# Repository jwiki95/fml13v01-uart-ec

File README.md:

## Expansion Card for UART Channel on DC RISC-V Mainboard

This is a KiCad Project with a basic schematic and board layout for connecting to the UART channel 
on the FML13V01 RISC-V Mainboard. This layout is intended to be used with any USB-UART controller
using 0.1 inch pin headers or the Raspberry Pi Debug Probe UART channel using the included JST
cable. This project started with the 
[Expansion Card template](https://github.com/FrameworkComputer/ExpansionCards/tree/main/Electrical) 
provided by Framework and the 
[documented pinout](https://github.com/DC-DeepComputing/Framework/blob/main/FML13V01/Framework%20Serial%20Port%20Connection%20Guide.pdf)
from Deep Computing. This design is a work-in-progress as I have not had samples manufactured at this time.

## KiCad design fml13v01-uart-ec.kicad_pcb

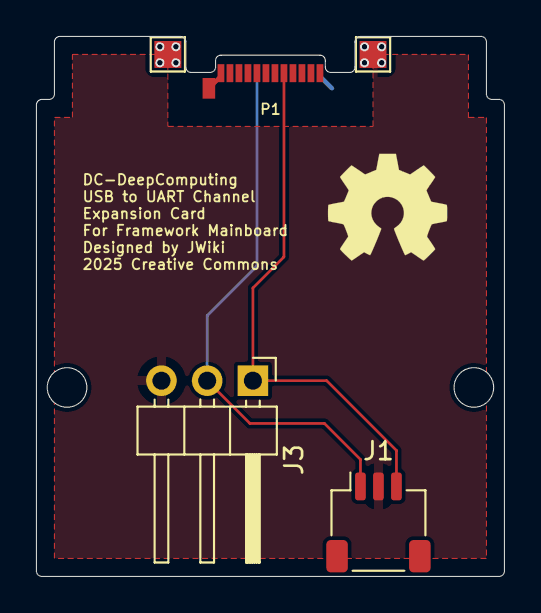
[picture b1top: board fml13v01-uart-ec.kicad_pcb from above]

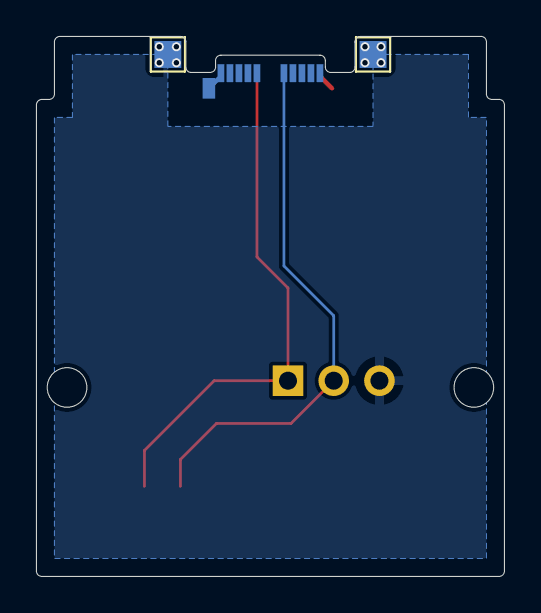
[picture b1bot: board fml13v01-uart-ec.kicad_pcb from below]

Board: 2 copper layers, 26.0 x 30.0 mm, 9 parts (2 on the bottom side), 4 nets.

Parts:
H1, H2: MountingHole; MountingHole_2.2mm_M2
J1: JST_UART; JST_SH_SM03B-SRSS-TB_1x03-1MP_P1.00mm_Horizontal
J3: PinHeader_UART; PinHeader_1x03_P2.54mm_Horizontal
P1: USB_C_Plug; USB_C_Plug_Molex_105444
TP1, TP2, TP3, TP4: TestPoint; TestPoint_Pad_1.5x1.5mm

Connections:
GND: J1.2, J3.3, P1.A1 (GND), P1.A12 (GND), P1.B1 (GND), P1.B12 (GND), P1.S1 (SHIELD), TP1.1, TP2.1, TP3.1, TP4.1
unnamed: J1.1, J3.2, P1.B8 (SBU2)
unnamed: J1.3, J3.1, P1.A8 (SBU1)
unnamed: P1.A4 (VBUS), P1.A9 (VBUS), P1.B4 (VBUS), P1.B9 (VBUS)

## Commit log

2025-02-23 Corrected Rx/Tx lines on JST connector for RPi Dbg UART

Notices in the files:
fml13v01-uart-ec.kicad_pcb:
This work is licensed under a Creative Commons Attribution 4.0 International License
2025 Creative Commons
